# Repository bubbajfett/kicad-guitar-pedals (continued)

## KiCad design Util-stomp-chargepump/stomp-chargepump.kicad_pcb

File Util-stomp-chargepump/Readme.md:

# Chargepump/stomp board.

*  prevents reverse polarity
*  3pdt + led
*  -9v optional out
*  18v optional out
*  Both ICL7660 and LT1054

This has been tested but not thoroughly.    This layout is based on
several vero layout on Tagboardeffects.blogspot.com

All registered trademarks are owned by their respective owners.

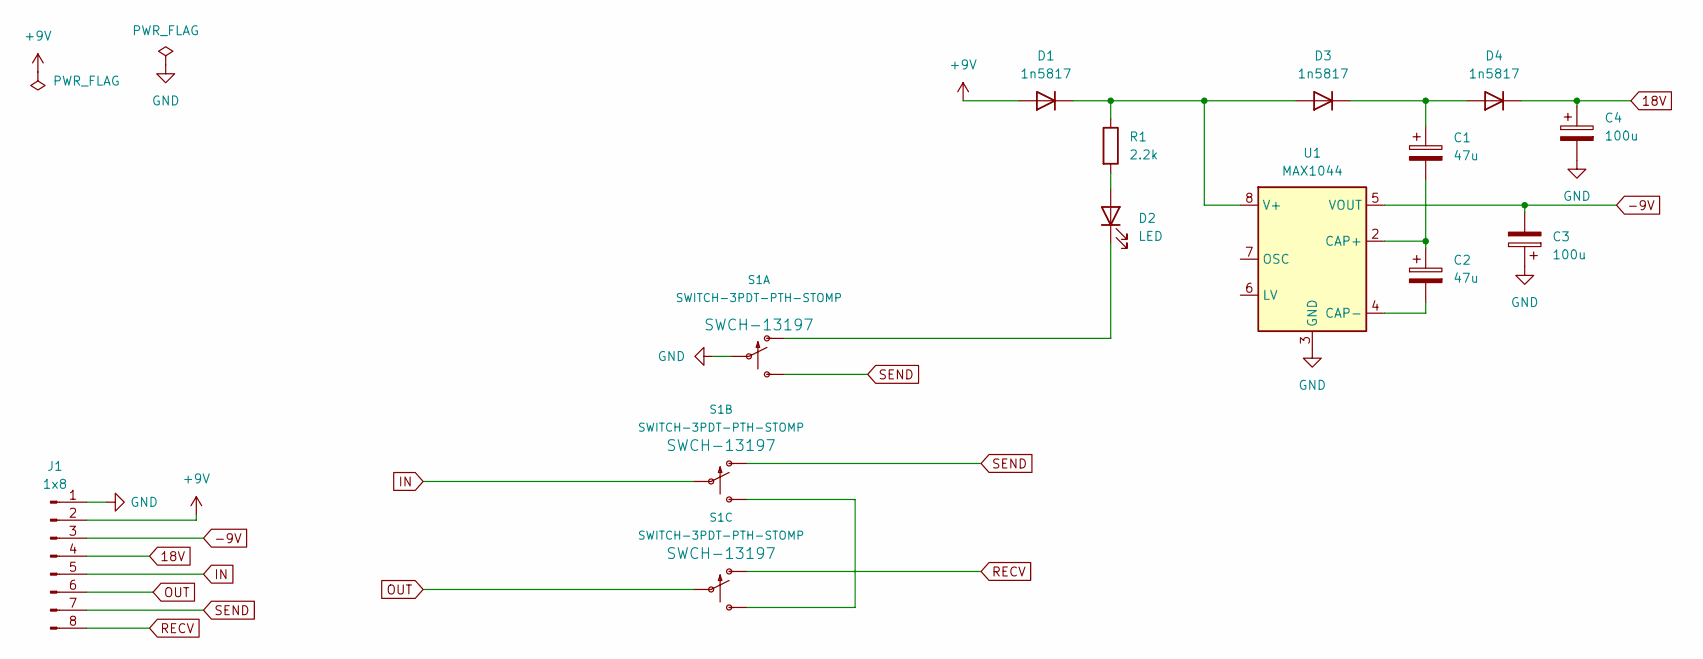
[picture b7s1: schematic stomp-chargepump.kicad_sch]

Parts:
C1, C2: 47u; CP_Radial_D5.0mm_P2.00mm
C3, C4: 100u; CP_Radial_D6.3mm_P2.50mm
D1, D3, D4: 1n5817; D_5W_P10.16mm_Horizontal
D2: LED; LED_D3.0mm
J1: 1x8; PinHeader_1x08_P2.54mm_Vertical
R1: 2.2k; R_Axial_DIN0207_L6.3mm_D2.5mm_P10.16mm_Horizontal
S1: SWITCH-3PDT-PTH-STOMP; STOMP_SWITCH_3PDT
U1: MAX1044

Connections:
18V: C4.1, D4.1 (K), J1.4
+9V: D1.2 (A), J1.2
-9V: C3.2, J1.3, U1.5 (VOUT)
GND: C3.1, C4.2, J1.1, S1.P$2, U1.3 (GND)
IN: J1.5, S1.P$5
unnamed: C1.1, D3.1 (K), D4.2 (A)
unnamed: C1.2, C2.1, U1.2 (CAP+)
unnamed: C2.2, U1.4 (CAP-)
unnamed: D2.1 (K), S1.P$1 (O)
unnamed: D2.2 (A), R1.2
unnamed: D1.1 (K), D3.2 (A), R1.1, U1.8 (V+)
unnamed: S1.P$6 (S), S1.P$9 (S)
OUT: J1.6, S1.P$8
RECV: J1.8, S1.P$7 (O)
SEND: J1.7, S1.P$3 (S), S1.P$4 (O)

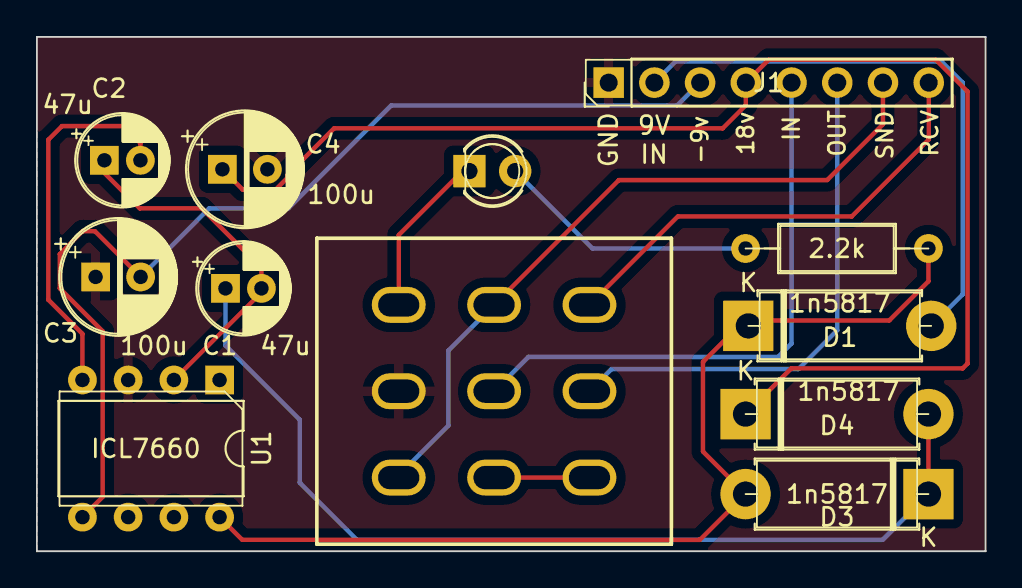
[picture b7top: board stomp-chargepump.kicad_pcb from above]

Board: 2 copper layers, 52.7 x 28.6 mm, 12 parts (0 on the bottom side), 15 nets.

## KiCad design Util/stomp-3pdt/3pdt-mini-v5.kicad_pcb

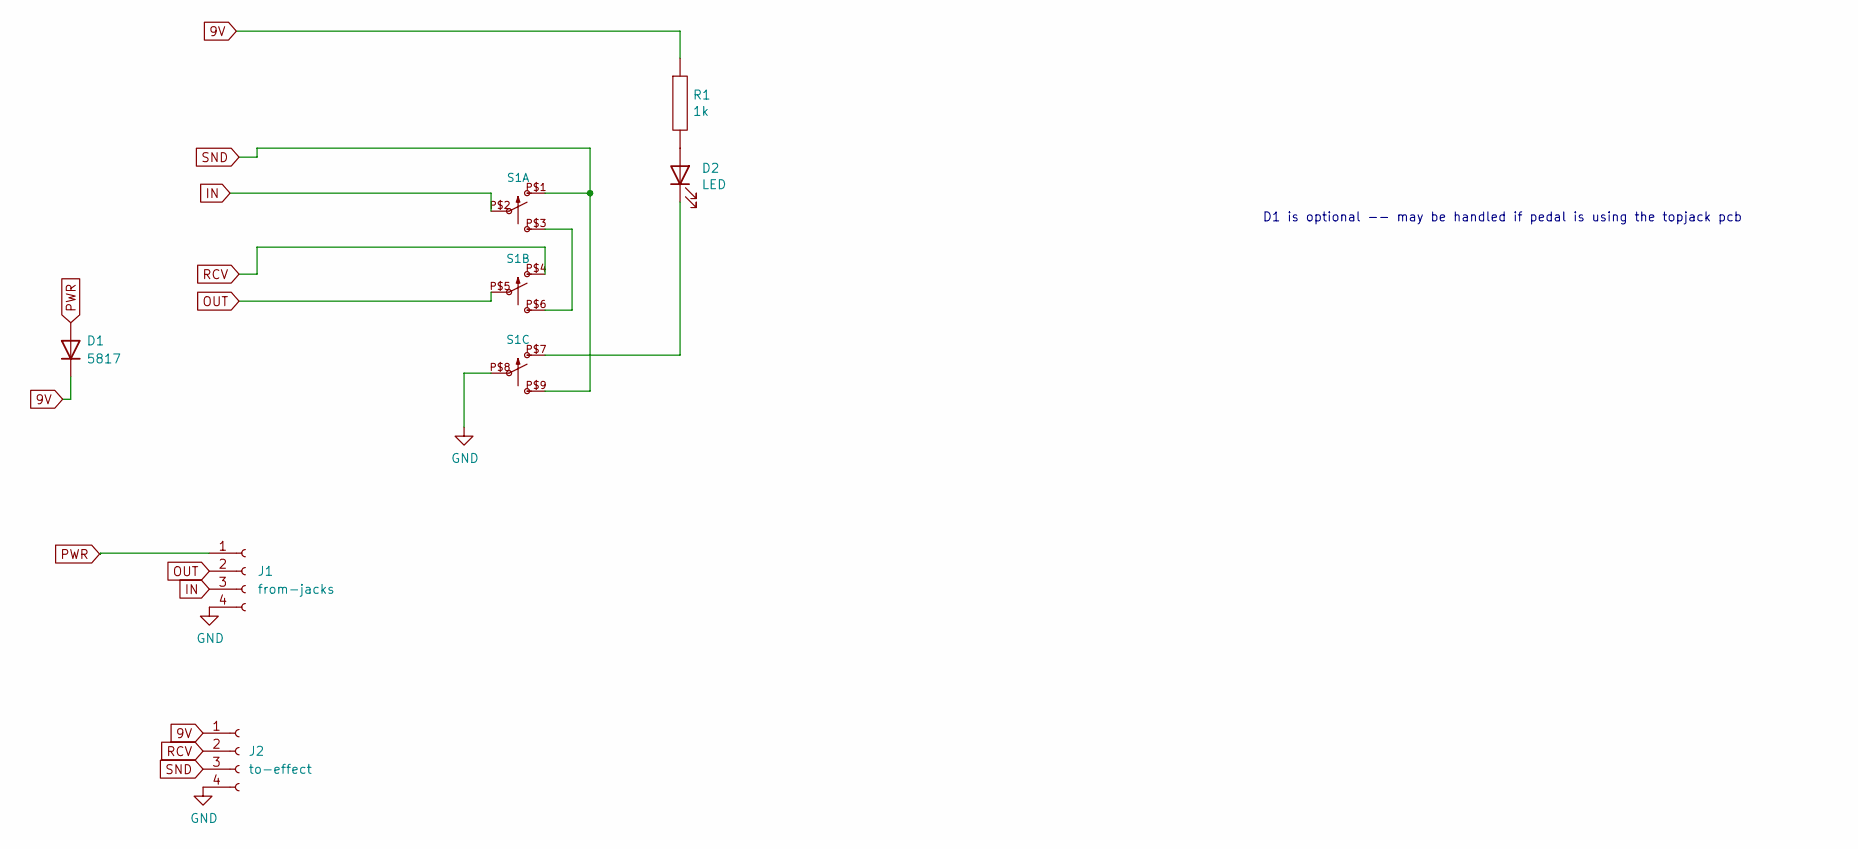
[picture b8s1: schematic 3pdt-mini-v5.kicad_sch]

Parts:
D1: 5817; D_DO-35_SOD27_P7.62mm_Horizontal
D2: LED; LED_D3.0mm
J1: from-jacks; PinHeader_1x04_P2.54mm_Vertical
J2: to-effect; PinHeader_1x04_P2.54mm_Vertical
R1: 1k; R_Axial_DIN0207_L6.3mm_D2.5mm_P10.16mm_Horizontal
S1: SWITCH-3PDT-PTH-STOMP; 3PDT

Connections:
9V: D1.1 (K), J2.1, R1.1
GND: J1.4, J2.4, S1.P$8
IN: J1.3, S1.P$2
unnamed: D2.2 (A), R1.2
unnamed: D2.1 (K), S1.P$7 (O)
unnamed: S1.P$3 (S), S1.P$6 (S)
OUT: J1.2, S1.P$5
PWR: D1.2 (A), J1.1
RCV: J2.2, S1.P$4 (O)
SND: J2.3, S1.P$1 (O), S1.P$9 (S)

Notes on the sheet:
D1 is optional -- may be handled if pedal is using the topjack pcb

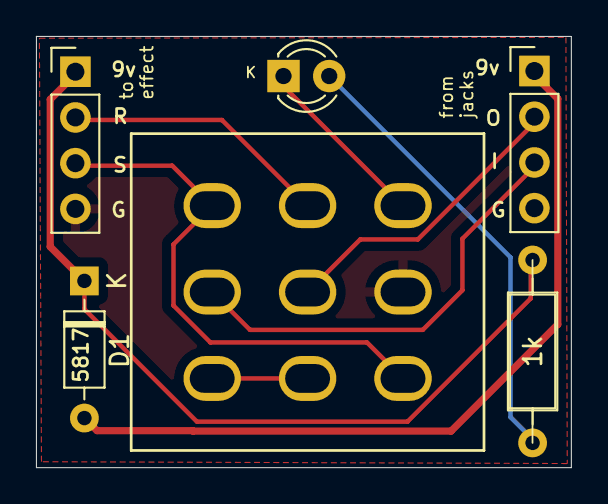
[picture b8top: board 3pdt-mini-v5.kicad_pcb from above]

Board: 2 copper layers, 29.7 x 24.0 mm, 6 parts (0 on the bottom side), 10 nets.
